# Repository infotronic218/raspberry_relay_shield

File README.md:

# Raspberry Pi 3 4 relays channels shield designed with Kicad

## The project is design using Kicad 5.1.5 

## The relay is drived by transistors

## Schematic

## Components side 

## 3D View of the circuit

## To contact me 
[My portfolio at this url ](https://www.oussenisawadogo.me)

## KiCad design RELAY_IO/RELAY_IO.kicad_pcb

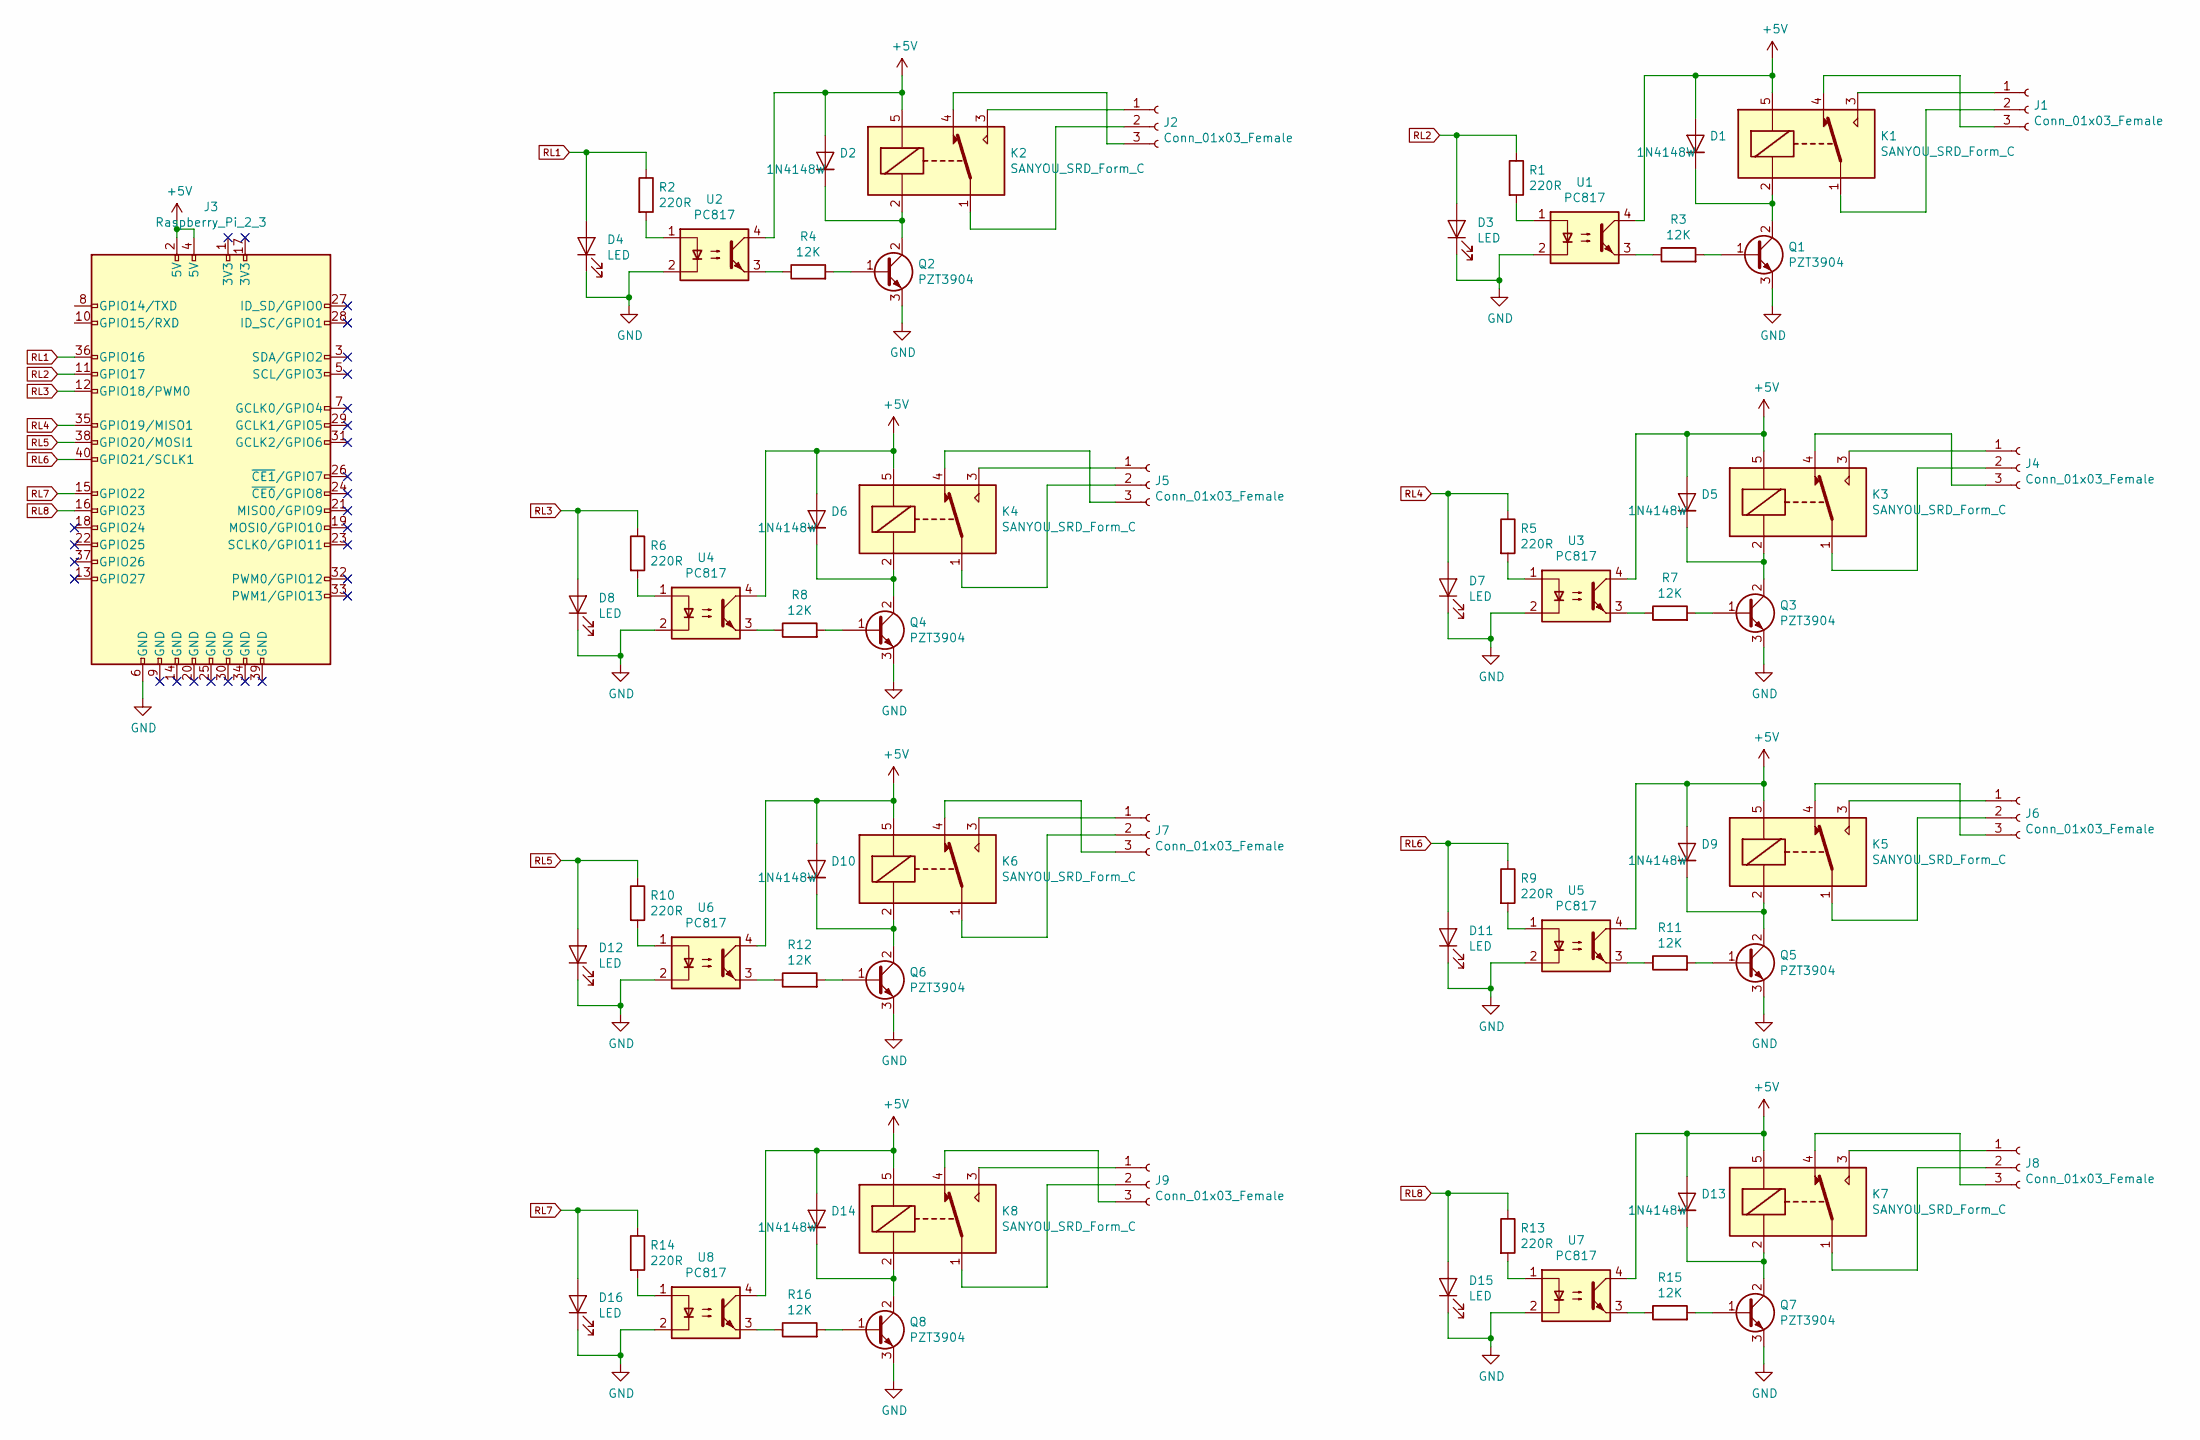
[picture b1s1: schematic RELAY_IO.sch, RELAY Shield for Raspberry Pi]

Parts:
D1, D2, D5, D6, D9, D10, D13, D14: 1N4148W; D_SOD-123
D3, D4, D7, D8, D11, D12, D15, D16: LED; LED_0805_2012Metric
J1, J2, J4, J5, J6, J7, J8, J9: Conn_01x03_Female; TerminalBlock_Phoenix_PT-1,5-3-5.0-H_1x03_P5.00mm_Horizontal
J3: Raspberry_Pi_2_3; PinSocket_2x20_P2.54mm_Vertical
K1, K2, K3, K4, K5, K6, K7, K8: SANYOU_SRD_Form_C; Relay_SPDT_SANYOU_SRD_Series_Form_C
Q1, Q2, Q3, Q4, Q5, Q6, Q7, Q8: PZT3904; SOT-223
R1, R2, R5, R6, R9, R10, R13, R14: 220R; R_1206_3216Metric_Pad1.42x1.75mm_HandSolder
R3, R4, R7, R8, R11, R12, R15, R16: 12K; R_1206_3216Metric_Pad1.42x1.75mm_HandSolder
U1, U2, U3, U4, U5, U6, U7, U8: PC817; DIP-4_W7.62mm

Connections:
+5V: D1.2 (A), D2.2 (A), D5.2 (A), D6.2 (A), D9.2 (A), D10.2 (A), D13.2 (A), D14.2 (A), J3.2 (5V), J3.4 (5V), K1.5, K2.5, K3.5, K4.5, K5.5, K6.5, K7.5, K8.5, U1.4, U2.4, U3.4, U4.4, U5.4, U6.4, U7.4, U8.4
GND: D3.1 (K), D4.1 (K), D7.1 (K), D8.1 (K), D11.1 (K), D12.1 (K), D15.1 (K), D16.1 (K), J3.6 (GND), Q1.3 (E), Q2.3 (E), Q3.3 (E), Q4.3 (E), Q5.3 (E), Q6.3 (E), Q7.3 (E), Q8.3 (E), U1.2, U2.2, U3.2, U4.2, U5.2, U6.2, U7.2, U8.2
unnamed: D1.1 (K), K1.2, Q1.2 (C), Q1.4 (C)
unnamed: D2.1 (K), K2.2, Q2.2 (C), Q2.4 (C)
unnamed: D5.1 (K), K3.2, Q3.2 (C), Q3.4 (C)
unnamed: D6.1 (K), K4.2, Q4.2 (C), Q4.4 (C)
unnamed: D9.1 (K), K5.2, Q5.2 (C), Q5.4 (C)
unnamed: D10.1 (K), K6.2, Q6.2 (C), Q6.4 (C)
unnamed: D13.1 (K), K7.2, Q7.2 (C), Q7.4 (C)
unnamed: D14.1 (K), K8.2, Q8.2 (C), Q8.4 (C)
unnamed: J1.1, K1.3
unnamed: J1.2, K1.1
unnamed: J1.3, K1.4
unnamed: J2.1, K2.3
unnamed: J2.2, K2.1
unnamed: J2.3, K2.4
unnamed: J4.1, K3.3
unnamed: J4.2, K3.1
unnamed: J4.3, K3.4
unnamed: J5.1, K4.3
unnamed: J5.2, K4.1
unnamed: J5.3, K4.4
unnamed: J6.1, K5.3
unnamed: J6.2, K5.1
unnamed: J6.3, K5.4
unnamed: J7.1, K6.3
unnamed: J7.2, K6.1
unnamed: J7.3, K6.4
unnamed: J8.1, K7.3
unnamed: J8.2, K7.1
unnamed: J8.3, K7.4
unnamed: J9.1, K8.3
unnamed: J9.2, K8.1
unnamed: J9.3, K8.4
unnamed: Q1.1 (B), R3.2
unnamed: Q2.1 (B), R4.2
unnamed: Q3.1 (B), R7.2
unnamed: Q4.1 (B), R8.2
unnamed: Q5.1 (B), R11.2
unnamed: Q6.1 (B), R12.2
unnamed: Q7.1 (B), R15.2
unnamed: Q8.1 (B), R16.2
unnamed: R1.2, U1.1
unnamed: R2.2, U2.1
unnamed: R3.1, U1.3
unnamed: R4.1, U2.3
unnamed: R5.2, U3.1
unnamed: R6.2, U4.1
unnamed: R7.1, U3.3
unnamed: R8.1, U4.3
unnamed: R9.2, U5.1
unnamed: R10.2, U6.1
unnamed: R11.1, U5.3
unnamed: R12.1, U6.3
unnamed: R13.2, U7.1
unnamed: R14.2, U8.1
unnamed: R15.1, U7.3
unnamed: R16.1, U8.3
RL1: D4.2 (A), J3.36 (GPIO16), R2.1
RL2: D3.2 (A), J3.11 (GPIO17), R1.1
RL3: D8.2 (A), J3.12 (GPIO18/PWM0), R6.1
RL4: D7.2 (A), J3.35 (GPIO19/MISO1), R5.1
RL5: D12.2 (A), J3.38 (GPIO20/MOSI1), R10.1
RL6: D11.2 (A), J3.40 (GPIO21/SCLK1), R9.1
RL7: D16.2 (A), J3.15 (GPIO22), R14.1
RL8: D15.2 (A), J3.16 (GPIO23), R13.1

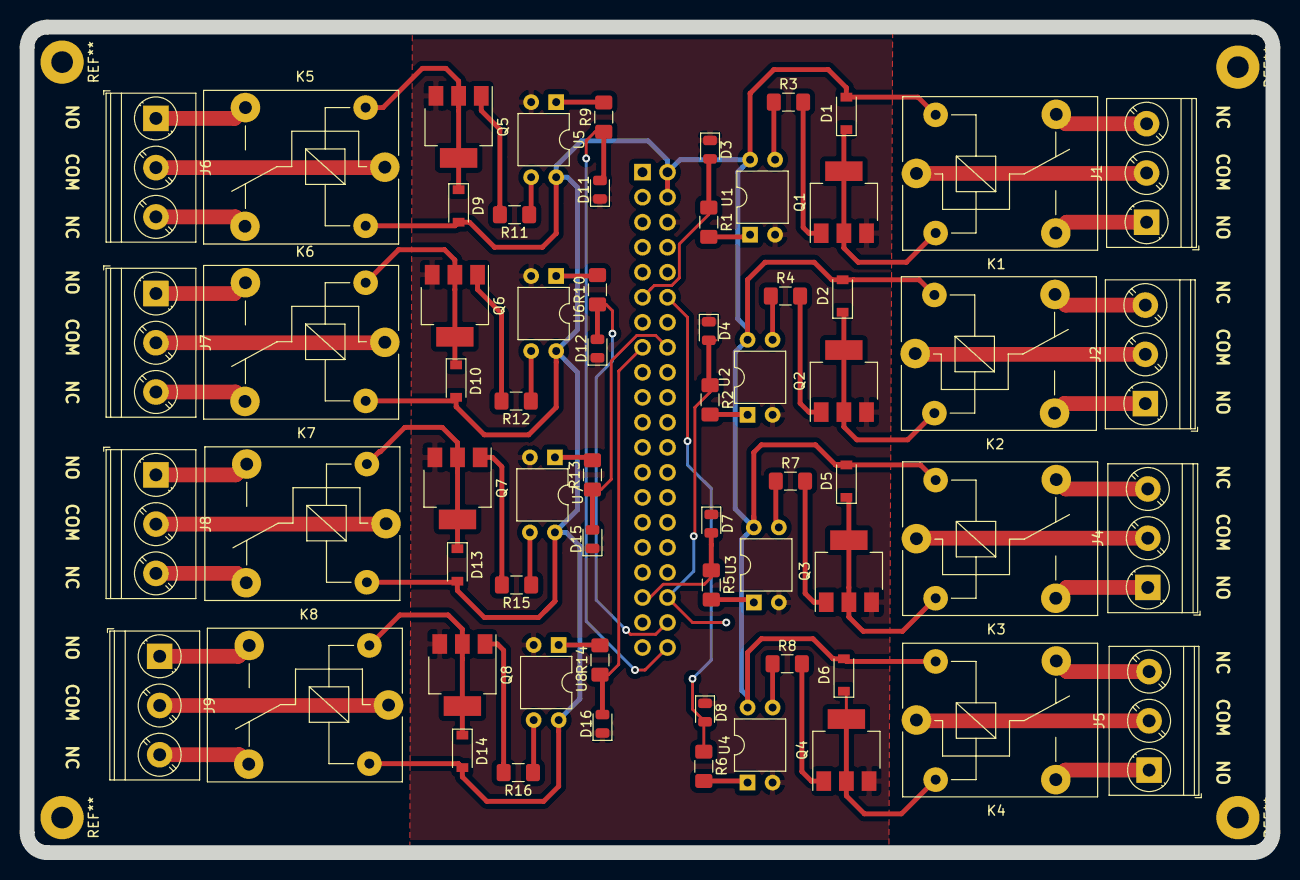
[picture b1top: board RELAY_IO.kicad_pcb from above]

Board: 2 copper layers, 126.5 x 83.8 mm, 65 parts (1 on the bottom side), 66 nets.

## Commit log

2020-08-01 Push project to github
2020-08-02 Update of ny page
2020-08-02 Images update
